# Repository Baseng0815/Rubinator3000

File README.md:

##### GYMNASIUM EDERTALSCHULE, FRANKENBERG-HESSEN

# Jugend forscht 2020

```
Philipp Geil, 19 Jahre
Tim Depner, 18 Jahre
Bastian Engel, 19 Jahre
```
## Das Lösen eines Zauberwürfels

## - der Rubinator3000 -

Mathematik-Informatik
Projektbetreuer: Oliver Blinn, Edertalschule Frankenberg

## Kurzfassung

Bei unserem Projekt “​ _Das Lösen eines Zauberwürfels - der Rubinator3000_ ​”
versuchten wir, einen verdrehten Zauberwürfel automatisch zu lösen.
Dazu haben wir Software und Hardware entwickelt, die einen Würfel erkennen,
verarbeiten und einen Lösealgorithmus anwenden können.
Anforderungen an die Hardware:
● Drehung jeder Seite des Würfels mit Schrittmotoren
● Elektronik zur Steuerung der Motoren
● Kameras zur Erkennung des verdrehten Würfels
Anforderungen an die Software:
● Auswertung der Kamerabilder und programmiertechnische Darstellung des
Würfels
● Lösealgorithmus entwickeln und Lösezüge berechnen
● Lösezüge am Würfel ausführen
...und natürlich das Vereinen aller Hardware-Komponenten in einer Maschine sowie
dessen Kommunikation mit dem Rechner, auf welchem die Steuerungssoftware
mit grafischer Benutzeroberfläche läuft.

## Erfolge:
1. Preis Regionalwettbewerb 2020
SMA Innovationspreis
Qualifikation Landeswettbewerb, der allerdings aufgrund von Corona abgesagt wurde

## 1. Einleitung

#### 1.1 Wieso einen Zauberwürfel lösen?

Unsere Faszination für Zauberwürfel hat vor ungefähr einem Jahr angefangen, als
wir bei einer extrakurrikularen E-Technik-Vorlesung ein YouTube-Video (Q1) sahen,
in dem jemand einen Zauberwürfel in 4.73 Sekunden löst. Da haben wir uns gefragt,
wie so etwas überhaupt möglich ist. Wir haben es als Kinder selbst probiert und
sogar bis zu drei Seiten gelöst bekommen, aber vollständig klappte es nie. Bei
nachfolgender Recherche im Internet sind wir auf Methoden gestoßen, welche von
sogenannten “Speedcubern” verwendet werden, um den Würfel in einer unglaublich
kurzen Zeit zu lösen.
Vertieft wurde unser Interesse weiter durch die unzähligen Variationen des Würfels.
Abseits der bekannten 3x3-Version ist der Zauberwürfel auch in einigen anderen
Größen von 2x2 bis zu 15x15 erhältlich. Dazu gibt es das Drehpuzzle nicht nur in
Hexaeder-Form, sondern auch in anderen polyedrischen Formen, wie beispielsweise
dem Tetraeder. Einige stellen sich sogar der Herausforderung, den Würfel mit nur
einer Hand, mit den Füßen oder mit verbundenen Augen zu lösen.
Wir selbst schaffen es per Hand, den Zauberwürfel in einer Zeit von circa 45
Sekunden zu lösen. Schaffen wir es, diese Zeit mit unserer Maschine zu
unterbieten?

#### 1.2 Gängige Lösemethoden

Die Lösung des Zauberwürfels erfolgt nicht improvisiert, sondern läuft nach einem
strikten Schema. Dies ist notwendig, um bereits gelöste Teile nicht erneut zu
verdrehen. Manche Teile lassen sich zwar ohne Vorkenntnisse lösen, aber den
Hauptteil löst man mit vorher entwickelten und auswendig gelernten Algorithmen und
Methoden, die den Würfel auf eine bestimmte Art und Weise permutieren.
Die am häufigsten verwendeten Lösemethoden sind zum einen die
“Fridrich”-Methode, welche von Jessica Fridrich entwickelt wurde, und zum anderen
die “Layer-by-Layer”-Methode.
Die Fridrich-Methode enthält viele Algorithmen, die man auswendig lernen muss,
welche jedoch eine kurze Lösezeit garantieren, weshalb sie auch von Speedcubern
verwendet wird.
Die Layer-by-Layer-Methode ist einfacher zu erlernen, erfordert aber mehr Züge, was
die Lösezeit natürlich verlängert.

- Kurzfassung
- 1. Einleitung
      - 1.1 Wieso einen Zauberwürfel lösen?
      - 1.2 Gängige Lösemethoden
      - 1.3 Das Ziel der Arbeit
- 2. Vorgehensweise, Materialien und Methode
      - 2.1 Die Position der Farben auf dem Würfel
      - 2.2 Drehungen der Seiten
      - 2.3 Die Lösung des Zauberwürfels
      - 2.3.1 Das weiße Kreuz
      - 2.3.2 Das F2L
      - 2.3.4 Die letzte Seite
      - 2.4 Die Entwicklung der Software
      - 2.5 Die Entwicklung der Hardware
      - 2.6 Der Bau der Hardware
      - 2.7 Die Digitalisierung des Würfels
- 3. Ergebnisse
      - 3.1 Software
      - 3.2 Hardware
- 4. Ergebnisdiskussion
- 5. Zusammenfassung
- 6. Danksagung
- 7. Quellen- und Literaturverzeichnis

Layer-by-Layer-Methode (Q3)
Ausgang Weißes
Kreuz
Weiße
Ecksteine
Mittlere
Schicht
Gelbes
Kreuz
Gelbe
Ecksteine
Ecksteine
drehen
Fridrich-Methode (Q4)
Ausgang Weißes Kreuz “First two
layers” (F2L)
“Orient last
layer” (OLL)
“Permutate
last layer”
(PLL)
Man erkennt, dass die Fridrich-Methode weniger Schritte benötigt. Dadurch wird sie
jedoch auch komplizierter und schwieriger zu erlernen. Die Layer-by-Layer-Methode
erfordert neun verschiedene Algorithmen, während es bei der Fridrich-Methode
schon 78 sind.

#### 1.3 Das Ziel der Arbeit

Wie schon erwähnt, brauchen wir ganze 45 Sekunden, um den Zauberwürfel per
Hand zu lösen und vergessen häufig Algorithmen. Diesen Problemen wollen wir
durch maschinelles Lösen entgegentreten. Motoren können die Drehungen am
Würfel besser koordinieren als wir mit unseren Händen. Außerdem können Rechner
Algorithmen ohne Probleme speichern und ausführen. Besonders beeindruckt hat
uns dabei der Löseroboter von Ben Katz, welcher in der Lage ist, den Würfel in 0.
Sekunden zu lösen (Q5).
Unser Ziel ist es, den Zauberwürfel innerhalb von 30 Sekunden lösen zu können, d.h.
konkret, eine dafür nötige Farberkennung zu entwickeln, eine entsprechende
Lösesoftware zu schreiben und eine Ansteuerung zu bauen, welche diese
Anforderung erfüllen kann.

## 2. Vorgehensweise, Materialien und Methode

#### 2.1 Die Position der Farben auf dem Würfel

Sei die Menge der Seiten des Würfels und die Menge der Flächen einer Seite.
Damit sind die Positionen der einzelnen Flächen auf dem Würfel bestimmt durch:
Um den Würfel darstellen zu können, müssen die Positionen noch durch die Menge
der Farben des Würfels ergänzt werden:
Damit besteht die Darstellung des Würfels aus einem Array der Länge 6, in welchem
die neun Farbwerte für jede Seite gespeichert sind. Das Programm geht davon aus,
dass sich die orange Fläche links befindet und die weiße Fläche oben. Da die
Implementation des Lösungsalgorithmus leichter fällt, wenn man nicht mit den
einzelnen Flächen arbeitet, sondern jene Flächen zu Steinen zusammenfasst,
welche über die Würfelkanten aneinander grenzen, haben wir uns dazu entschieden,
eine Struktur für die Ecksteine (3 Flächen) und eine für die Kantensteine (2 Flächen)
zu erstellen. In diesen Strukturen werden ein Tupel der Farben des Steines sowie ein
Verweis auf den Würfel, zu dem dieser Stein gehört, gespeichert. Die Steine werden
bei der Initialisierung der Cube-Klasse automatisch aus den vorgegebenen
Positionen erstellt, die für jeden Stein festgelegt sind. Die Steine werden durch ihre
Farben charakterisiert, da die Positionen zum einen durch die Indizes des Arrays
festgelegt sind und es zum anderen für den Lösungsalgorithmus nötig ist, die
Position gewisser Steine anhand der Farben zu identifizieren. Diese Positionen
lassen sich durch einen Vergleich der Farben des Steines mit den vorgegebenen
Steinpositionen bestimmen.

#### 2.2 Drehungen der Seiten

Um den Zauberwürfel nun zu lösen oder zu verdrehen, mussten wir also noch eine
Möglichkeit implementieren, um einzelne Seiten des Würfels im Programm zu
drehen. Eine Drehung wird durch die zu drehende Seite und die Anzahl der
Vierteldrehungen (90°) im Uhrzeigersinn festgelegt.
Jeder Move beschreibt eine bestimmte Permutation des Würfels, da zum einen die
Farben auf der jeweiligen Seite, aber auch teilweise die Farben auf den
angrenzenden Seiten vertauscht werden.

Diese beiden Permutationen können jeweils durch Funktionen beschrieben werden:
Betrachtet man die Drehung einer Seite im Uhrzeigersinn, so lässt sich
bestimmen:
Der Funktionswert von _f_ 1 gibt hierbei die neue Position nach der Drehung an:
Die Funktionswerte von lassen sich nicht allgemein formulieren, da abhängig
von der gedrehten Seite ist. Die Relationen von sind im Programm hinterlegt und
werden auf die entsprechenden Seiten angewendet.

#### 2.3 Die Lösung des Zauberwürfels

#### 2.3.1 Das weiße Kreuz

Das weiße Kreuz wird durch ein Objekt der “CrossSolver”-Klasse gelöst. Dazu wird
zuerst ein Pivotelement festgelegt. Bei diesem Element handelt es sich entweder um
einen weißen Kantenstein, der sich bereits richtig auf der weißen Seite befindet und
bei dem sich die meisten Steine in der gewünschten Position befinden, oder um
einen weißen Kantenstein, der sich mit den wenigsten Zügen in die richtige Position
bringen lässt. Um die Anzahl der Züge zu bestimmen, die benötigt werden, um den
Stein relativ zum Pivotelement richtig auszurichten, gibt es eine Methode, die jeden
Stein bewertet und die Anzahl der Züge zurückgibt. Beim Lösen des weißen Kreuzes
bewertet der “CrossSolver” zuerst für jeden Kantenstein, wie viele Züge jeweils
benötigt werden und löst dann den Kantenstein, für den die wenigsten benötigt
werden. Zum Lösen der einzelnen Steine unterscheidet der “CrossSolver” zwischen
vier verschiedenen Fällen:

1. Der Stein befindet sich mit der weißen Fläche auf der weißen Seite, aberdie
    seitliche Farbe stimmt nicht.
2. Der Stein befindet sich mit der weißen Fläche auf der unteren Seite.
3. Der Stein befindet sich auf der mittleren Ebene, also mit keiner Fläche auf
    der oberen oder unteren Seite.
4. Der Stein befindet sich mit der weißen Fläche auf einer der seitlichen Seiten
    (orange, grün, rot, blau) und mit der anderen Fläche auf der oberen oder
    unteren Seite.
Die einzelnen Fälle werden dann durch vorgegebene Algorithmen gelöst.

#### 2.3.2 Das F2L

Das Lösen des F2L funktioniert analog zum Lösen des weißen Kreuzes. Das
Programm orientiert sich hier nun nicht mehr an nur einem Stein, sondern an jeweils
zwei Steinen, die gelöst werden sollen. Dazu bewertet es wieder jedes Steinpaar und
löst jenes, welches die wenigsten Züge benötigt. Diese Berechnung erfolgt
asynchron, um Rechenzeit zu sparen. Danach wird das Paar mit Hilfe von 13
Algorithmen gelöst.

#### 2.3.4 Die letzte Seite

Für das Lösen der letzten Seite sind im Programm Muster und die dazugehörigen
Zugfolgen hinterlegt (57 OLL und 21 PLL). Die Muster für das OLL beziehen sich nur
auf die Anordnung der gelben Flächen. Dazu wird eine Folge von 9 Bits verwendet,
welche die gelbe Seite repräsentiert, und jeweils vier Folgen von je 3 Bits, welche die
3 Flächen der über die Würfelkanten angrenzenden Seiten repräsentieren. Das
Programm vergleicht dann jegliche Muster mit dem Würfel und kann somit die
Zugfolge angeben. Die PLL-Muster sind etwas komplexer als die OLL-Muster, da das
PLL die einzelnen Farben einbezieht. Dazu wird jeder der vier seitlichen Farben eine
Zahl zugeordnet ((orange, 0), (grün, 1), (rot, 2), (blau, 3)). Im Programm sind dann
die Differenzen zwischen den drei Steinen für alle vier Seiten hinterlegt. Mit diesen
Mustern kann daraufhin die Zugfolge bestimmt werden, die zur Lösung des
Zauberwürfels führt.

#### 2.4 Die Entwicklung der Software

Wir haben mithilfe von Visual Studio Community 2019, einer von Microsoft
entwickelten IDE, programmiert. Das Projektmanagement wird dadurch vereinfacht
und der integrierte Designer erlaubt einfache und gute GUI-Erstellung. Da jeder von
uns schon im Voraus Erfahrung mit dieser Entwicklungsumgebung hatte, mussten
wir uns nicht umstellen und der Entwicklungsprozess konnte sofort starten.
Als Programmiersprache entschieden wir uns für C#, um WPF (Windows
Presentation Foundation) nutzen zu können. Das ist eine GUI-Library, mit der viele
Windows-Programme geschrieben werden. Ein großer Vorteil davon ist, dass das
GUI-Design extern in XAML-Dateien definiert und damit vollständig von der Logik
des Programms abgekoppelt ist. Dies ermöglichte uns, die Arbeit besser aufzuteilen.
So kann ein Programmierer am GUI arbeiten, während ein anderer die Logik dazu
schreibt. Die 2D-und 3D-Ansicht des Würfels erstellten wir mit OpenGL, einer
Graphics-Library, die auch in vielen Computerspielen verwendet wird und sehr
weitreichende Funktionen besitzt.

Da wir zu dritt waren und viele Änderungen parallel zusammenkamen, benötigten wir
ein Versionskontrollsystem, um diese zu verwalten und gegebenenfalls bei Bugs
frühere Versionen wiederherstellen zu können. Entschieden haben wir uns für Git,
welches auch industriell verwendet wird. Damit war es kein Problem mehr, Aufgaben
aufzuteilen und zu synchronisieren.

#### 2.5 Die Entwicklung der Hardware

Das CAD-Modell unseres ​ _“Rubinator3000”_ haben wir mit dem kostenlosen Programm
“FreeCAD” entworfen, da dieses für unsere Anforderungen genügt und wir unser
Projekt kostengünstig gestalten wollten. Zudem war es uns mit FreeCAD möglich, die
Bauteile in das STL-Format zu exportieren, um sie mit einem 3D-Drucker drucken zu
können. Da unsere Hardware fast ausschließlich aus 3D-Druck Bauteilen besteht,
war diese Funktion sehr hilfreich. Die Schaltpläne für die Ansteuerung der
Schrittmotoren erstellten wir mit Eagle. Eagle bietet zudem die Möglichkeit,
Leiterplatten zu designen, um diese bei einem Leiterplattenhersteller anfertigen zu
lassen.
Die Ansteuerung der Schrittmotoren musste über eine Verstärkerschaltung getätigt
werden. Das lag zum einen daran, dass die Schrittmotoren eine Spannung von 12V
benötigen, während der Arduino nur 5V liefert. Zum anderen wird ein sehr großer
Strom benötigt, um die Magnetfelder innerhalb der Schrittmotoren mit Hilfe von
Spulen zu erzeugen.

#### 2.6 Der Bau der Hardware

Wir haben uns für 3D-gedruckte Bauteile
entschieden, da diese eine höhere Präzision
der Mechanik ermöglichten. Unser erster
Prototyp bestand ausschließlich aus Holz
und es kam aufgrund mangelhafter
Genauigkeit der Mechanik zum
sogenannten “Verkantungsproblem”: Eine
Seite des Würfels verkantete sich nach einer
unvollständigen Drehung. Dieses Problem
lösten wir letztendlich durch die zweite
Version der Hardware und einen anderen Zauberwürfel. Zudem ließen die
verwendeten Miniaturbalg-Kupplungen zu viel Spielraum zu, was zu
Ungenauigkeiten bei den Würfeldrehungen führte. Deshalb ersetzten wir sie durch
Elastomerkupplungen, da diese deutlich genauer sind, wodurch sich der Würfel viel
besser drehen lässt.
Zudem haben wir uns Platinen zur Ansteuerung der Schrittmotoren anfertigen
lassen, da die anfangs selbst gelöteten Platinen teilweise unzuverlässig waren und
sehr viel Platz im Gehäuse in Anspruch nahmen. Hinzu kam noch, dass die selbst
gelöteten Platinen viel Wärme entwickelten, da jede einzelne von ihnen einen

separaten Spannungsregler besaß, der für den Anschluss eines Mikrocontrollers
gedacht war.
Im nebenstehenden Bild ist eine
Schaltung abgebildet, welche zeigt,
wie mithilfe des Transistors (T1) der
Stromkreis der Spule des
Schrittmotors (L1) geschlossen wird^1.
Dadurch wird es möglich, dass Strom
fließen kann, welcher das
magnetische Feld im Schrittmotor
erzeugt. Der Basiswiderstand (R1)
dient zur Begrenzung des
Basisstroms des Transistors, da der
Ausgang des Arduino einen Strom
von maximal 40mA zur Verfügung
stellt.
Wir ließen die Bodenplatte bei der Firma Viessmann drucken, weil diese für unseren
3D-Drucker zu groß war. Sie stellte uns für diesen Druck einen besseren 3D-Drucker
zur Verfügung. Nach dem Druck haben wir sie auf eine solide Holzbox gesetzt,
welche auch die Elektronik enthält. Dadurch wird Stabilität garantiert und die Motoren
können passend positioniert werden.

#### 2.7 Die Digitalisierung des Würfels

Unsere erste Methode zur Digitalisierung des Würfels sah folgendermaßen aus:

(^1) Die Freilaufdiode wurde zur Vereinfachung der Schaltung weggelassen

Wir lasen jede einzelne Seite mit der Kamera eines Smartphones ein, um daraus den
Würfel digital zusammensetzen zu können. Dafür haben wir eine Android-App in der
Programmiersprache Java geschrieben.
Ein Computer – also auch das Smartphone, welches wir benutzen – stellt Farben im
RGB-Format dar. Anhand dieser Werte werden die einzelnen Würfel-Farben
(Orange, Weiß, Grün, Gelb, Rot und Blau) auch unterschieden.
Um sich auch wechselnden Lichtverhältnissen anpassen zu können, war es nötig zu
Beginn Referenz-RGB-Werte festzulegen, anhand welcher die App die Farben
unterschied.
Im nächsten Schritt hielten wir die Handykamera vor jede Würfelseite. Die App las
die RGB-Werte der einzelnen Flächen aus und ordnete ihnen anhand der anfangs
eingelesenen Referenz-RGB-Werten die entsprechende Farbe zu.
Sobald die App eine Würfelseite eingelesen hatte, schickten wir dessen Farben über
ein WLAN-Netzwerk an jenen Laptop, auf welchem das Hauptprogramm lief.
Nachdem wir auf diese Weise alle sechs Seiten eingelesen und an den Laptop
geschickt hatten, könnte dieser daraus den Würfel digital zusammensetzen.
Die zweite Version unseres Projekts brachte auch ein Upgrade in der Farberkennung
mit sich. Anstatt mit einer Handy-App jede Seite einzeln einzulesen, brachten wir vier
stationäre USB-Kameras an der Maschine an, mit welchen wir die RGB-Werte der
einzelnen Flächen des Würfels automatisch einlesen. Dies beschleunigt den Prozess
der Digitalisierung des Würfels natürlich enorm.
Auch an der Erfassung und Verarbeitung der eingelesenen RGB-Werte haben wir
Änderungen vorgenommen:
Für jede einzelne Fläche des Würfels
legen wir eine Position auf einem der 4
Kamera-Streams fest, an welcher die
RGB-Werte der jeweiligen Fläche
ausgelesen werden sollen. Da die 8
Mittelsteine des Würfels ihre Position
während des Drehen nie verändern,
werden deren RGB-Werte gar nicht mehr
eingelesen.
So lesen wir alle RGB-Werte an den 48
Positionen ein und berechnen die
jeweilige Wahrscheinlichkeit dafür, dass
die jeweiligen RGB-Werte zu einer orangen, weißen, grünen, gelben, roten oder
blauen Fläche gehören.
Die 8 Flächen an den Positionen mit den höchsten Orange-Wahrscheinlichkeiten
bestimmen wir als orange Flächen. So gehen wir die restlichen 5 Farben ebenfalls
durch und haben zum Schluss 8 Flächen von jeder Farbe, mit welchen wir wiederum
den Würfel digital darstellen.

Durch dieses Verfahren wird die Farberkennung viel präziser, da wir davon
ausgehen, dass wir genau 8 Flächen von allen Farben haben.
Ein Problem, welches wir bei der Farberkennung hatten war Folgendes:
Aufgrund der sehr glatten Oberfläche der Würfelflächen, spiegelten diese das
Umgebungslicht teilweise gebündelt direkt in eine der Kameralinsen. Dadurch war im
Kamerabild nicht die entsprechende Farbe der Seite zu sehen, sondern ein helles,
weißliches Leuchten. Dies verfälschte die RGB-Werte, welche für die dazugehörige
Fläche eingelesen wurden. Eine eigentlich blaue Fläche erschien somit
unerwünschterweise weiß. Wir haben dieses Problem gelöst, indem wir einen
Vorhang über die ganze Maschine gehängt haben, um den Spiegelungseffekt zu
minimieren. Damit wir jedoch überhaupt noch etwas mit den Kameras sehen können,
haben wir zusätzlich LEDs direkt in die Maschine gebaut, welche den Würfel mit
diffusem Licht bescheinen.
Dies soll jedoch nur vorübergehend die Lösung des Problems sein, da das Abdecken
und das Entfernen der Abdeckung recht viel Zeit braucht. Für die Zukunft planen wir,
nicht absolute Positionen, an welchen die Farben des Würfels ausgelesen werden,
zu benutzen. Stattdessen soll das Programm mittels Konturerkennung selbst
herausfinden, wo sich auf dem entsprechenden Kamerabild die einzelnen
Würfel-Flächen befinden, von welchen das Programm daraufhin die entsprechenden
Farben ausliest. Hierbei könnten wir zu helle Pixel aussortieren, wodurch das
“Spiegelungs-Problem” gelöst würde. Erste Tests in separat von uns programmierten
Anwendungen liefern vielversprechende Ergebnisse. Jetzt gilt es noch, die neue
Farberkennung in das Hauptprogramm zu implementieren.

## 3. Ergebnisse

#### 3.1 Software

Wir haben mithilfe der vorgestellten Vorüberlegungen und Methoden das
Hauptprogramm fertiggestellt, welches den Würfel lösen und die Lösealgorithmen
über eine serielle Schnittstelle an den Arduino schicken kann.
Die Effizienz der Algorithmen lässt sich an folgendem Graph ablesen:
Für jede Verdrehungsanzahl machten wir 30
Testdurchgänge, woraufhin daraus der
Mittelwert gebildet wurde. Die
Schwankungen lassen sich dadurch erklären,
dass nur ein einziger zusätzlich ausgeführter
Algorithmus mehrere Züge enthält und
dadurch das Ergebnis stark beeinflusst
werden kann.
Es ist zu erkennen, dass unsere Lösung ab
vier Verdrehungen erheblich mehr Züge
benötigt. Ab sechs Verdrehungen pendelt sich
die Anzahl der Lösezüge auf ungefähr 65 ein.
Die Schrittmotoren lassen sich mit 360° pro Sekunde drehen, was zwei Zügen
entspricht. Daher ist eine theoretische Lösezeit von ca. 15 Sekunden erreichbar, die
aber durch Ausnahmefälle wie zum
Beispiel die Doppeldrehung einer
Seite oder dem ​ _Multiturning_
Schwankungen unterliegt.
Außerdem ist zu erkennen, dass
der Zugzuwachs am stärksten vom
FTL beeinflusst wird, wobei die
OLL- und PLL-Algorithmen gegen
Ende weniger beitragen. Das Kreuz
hat kaum Einfluss.
Die grafische Oberfläche des
Programms enthält alle nötigen
Kontrollelemente, so zum Beispiel
das Verdrehen oder Lösen des Würfels oder Debug-Fenster zum Beheben von
fehlerhaften Algorithmen und Mustern. Dadurch können wir leicht und ohne

ständiges Überlegen Einstellungen ändern und Tests durchführen. Das ist zum
Beispiel besonders relevant für die Verbindung zum Mikrocontroller, da diese über
einen sich ändernden COM-Port stattfindet, welchen man anfangs auswählen muss.

#### 3.2 Hardware

Der Arduino wartet nach dem Verbinden mit dem Programm auf die Befehle und
führt diese aus. Er ist nötig, da die Schrittmotoren nicht direkt an den Computer
angeschlossen
werden können.
Zudem benötigen die
Schrittmotoren sehr
viel Strom. Deshalb ist
es notwendig, für
jeden Schrittmotor
eine Schaltung zu
bauen, die genug
Strom liefern kann,
um den Würfel zu
drehen. Anfangs
hatten wir die Motoren
nach einer Drehung
nicht abgeschaltet und
so entstand das
Problem, dass alle
inaktiven Motoren zu

viel Strom verbrauchten und somit nicht genug Drehmoment bereitstand, um den
Würfel zu drehen. Dieses Problem haben wir softwaretechnisch gelöst, indem wir
den Strom der Motoren nach jeder Drehung abschalteten und so der komplette
Strom des Netzgerätes für einen oder bei Multiturns zwei Motoren bereitsteht.

## 4. Ergebnisdiskussion

Unser ​ _“Rubinator3000”_ ist noch nicht das perfekte Ergebnis jahrelanger Forschung,
aber es kann sich trotzdem sehen lassen.
Wie anfangs bereits erwähnt, kam uns die Idee zum Bau einer solchen Maschine, bei
einer extrakurrikularen E-Technik-Vorlesung im Rahmen der Young Engineer
Academy (YEA). Wir haben dort überlegt, was wir als unser Abschlussprojekt bei der
YEA realisieren könnten. Da wir noch viel Zeit hatten, bis das Projekt vorgestellt
werden sollte, entschieden wir uns nach einigen Suchanfragen im Internet für den
Bau eines doch recht aufwendigen Zauberwürfel-Lösers. Einige weitere
Kursteilnehmer, welche sich ebenfalls für den Zauberwürfel begeistern, unterstützten
unsere Idee.
Anfangs schien unsere Aufgabe recht simpel, da man lediglich 6 Schrittmotoren
benötigte, die die Seiten des Zauberwürfels drehen sollten.
Bereits in den nächsten Wochen (Januar 2019) starteten wir mit der
Programmierung. Der eigentliche Bau der ersten Maschine begann dann Ende April
2019 und pünktlich zum Präsentationstermin am 28. Juni vollendeten wir die erste
Version der Hardware. Bis dahin hatten wir während der Schulzeit schon dutzende
Freistunden in unser Projekt investiert, da die Umsetzung des Projekts dann doch
komplizierter war, als wir zunächst vermutet hatten. Vor allem die Drehung des
Würfels machte uns zu schaffen, da die Hardware zu ungenau war und der Würfel
sich deshalb immer wieder verkantete. Dies war aber letztendlich nicht das größte
Problem, welches wir bei der Präsentation hatten.
Auf der Bühne scheiterte die Vorführung unserer Maschine am Lösen des
Zauberwürfels durch das Programm.
Also entschlossen wir uns, in den Sommerferien das Programm zu überarbeiten. Da
der bestehende Code mittlerweile sehr unübersichtlich war und wir nicht genau
wussten, wo die einzelnen Fehler lagen, entschlossen wir uns dazu, das Programm
von Grund auf neu zu entwickeln. Wir besaßen bereits das Vorwissen aus dem
ersten Versuch , weshalb uns die Entwicklung der zweiten Maschine leichter fiel.
Aufgrund der Verkantungen des Würfels kam uns die Idee, die Teile der Hardware,
welche eine hohe Genauigkeit erforderten, mit dem 3D-Drucker zu fertigen, da dieser
viel genauere Ergebnisse liefert als das Aussägen aus Holz. Zudem haben wir neue
Kupplungen eingebaut, die zur Erhöhung der Genauigkeit beitrugen.

Das Projekt erschien uns auf den ersten Blick leicht, aber es gab viele Faktoren, die
wir nicht berücksichtigt hatten. Darunter fiel zum Beispiel das Einlesen des Würfels,
das Bauen der Hardware mit einer hohen Genauigkeit und vieles andere.
Die Software könnte noch verbessert werden, indem man beispielsweise eine andere
Methode zum Lösen des Würfels verwendet, die weniger Züge benötigt. Diese
Verbesserung würde das maschinelle Lösen auch erheblich beschleunigen, da sich
die Motoren dadurch weniger drehen müssten.
Zudem könnte man auch Motoren verwenden, die sich schneller ansteuern lassen,
welche ebenfalls das Lösen beschleunigen würden.
Wir hatten während der Entwicklung die Idee das Hauptprogramm auf einem
Raspberry Pi laufen zu lassen, da dieser den Computer ersetzen würde, der die
Lösung berechnet. Diese Idee verwarfen wir aber schnell, da wir schon angefangen
hatten, die Software auf dem .NET Framework von Microsoft für Windows zu
entwickeln, während der Raspberry auf einem linuxbasierten Betriebssystem läuft.
Der Ansatz könnte aber in der Zukunft realisiert werden.
Auch die Ansteuerung der Motoren hat uns Probleme bereitet, da wir eine eigene
Platine entwickelt und einen Mikrocontroller programmiert haben. Dieser ist jedoch
beim Debuggen der Software durch eine Überspannung kaputt gegangen und wir
mussten ihn durch einen Arduino ersetzen.

## 5. Zusammenfassung

Zusammenfassend lässt sich sagen, dass unser Projekt noch viele
Erweiterungsmöglichkeiten bietet. Es könnten beispielsweise noch LEDs eingebaut
werden, die für eine bessere Beleuchtung des Würfels bei schlechten
Lichtverhältnissen sorgen.
Unser Ziel, dass unsere Maschine weniger Zeit zum Lösen des Würfels benötigt als
wir selbst per Hand, hat das Projekt noch nicht ganz erreicht. Es befindet sich aber
auf einem guten Weg zu einer Lösung, die unseren ursprünglichen Anforderungen
gerecht wird. Dies könnte durch weitere Verbesserungen der Hard- und Software
erreicht werden.
Das Projekt ​ _“Rubinator3000”_ hat zwar nur einen kleinen Nutzen für die Allgemeinheit,
aber es hat uns geholfen, unsere Kompetenzen im Bereich der Programmierung und
der Entwicklung von Hardware zu erweitern. Zudem haben wir die Erfahrung
gemacht, dass Dinge und Ideen oft einfacher erscheinen, als sie es eigentlich sind.
Es lohnt sich also, zuerst darüber nachzudenken, wie man sie angeht und realisiert.
Zuletzt durften wir die Erfahrung machen, was man mit Teamwork alles erreichen
kann. Während des Entwicklungsprozesses haben sich alle Team-Mitglieder nur auf

jeweils ein Teilgebiet spezialisiert. Trotzdem können wir durch unsere gelungene
Zusammenarbeit nun einen voll funktionsfähigen Zauberwürfellöser präsentieren.

## 6. Danksagung

Abschließend bedanken wir uns für jegliche Unterstützung während der Umsetzung
unseres Projekts.
Exemplarisch möchten wir hier die Fachschaft Physik der Edertalschule nennen,
welche uns bei Fragen in der Umsetzung beriet und uns kostenlos über einen
längeren Zeitraum den Zugang zu ihrem Werkraum gewährte, in welchem wir unsere
Maschine entwickeln und anfertigen konnten. Zudem danken wir unseren
Mitschülern der Young Engineer Academy, die uns beim Bau der ersten Version des
“Rubinator3000” unterstützt haben.
Darüber hinaus geht ein riesiges Dankeschön an die Viessmann Group, welche uns
finanziell bei der Anfertigung der Hardware unterstützte. Zusätzlich ermöglichte sie
uns die Teilnahme an der Young Engineer Academy, durch welche wir essentielle
Grundkenntnisse und letztendlich auch die Idee für dieses Projekt bekommen haben.

## 7. Quellen- und Literaturverzeichnis

##### Q1: 04.01.2020 16: https://www.youtube.com/watch?v=KfpJZHP6DLA
##### Q2: 04.01.2020 17: https://speedcube.de/
##### Q3: 04.01.2020 17: https://ruwix.com/the-rubiks-cube/how-to-solve-the-rubiks-cube-beginners-method/
##### Q4: 04.01.2020 17: https://ruwix.com/the-rubiks-cube/advanced-cfop-fridrich/
##### Q5: 04.01.2020 17: https://www.youtube.com/watch?v=nt00QzKuNVY
##### Q6: 14.01.2020 19: https://www.arduino.cc/en/Tutorial/DigitalPins

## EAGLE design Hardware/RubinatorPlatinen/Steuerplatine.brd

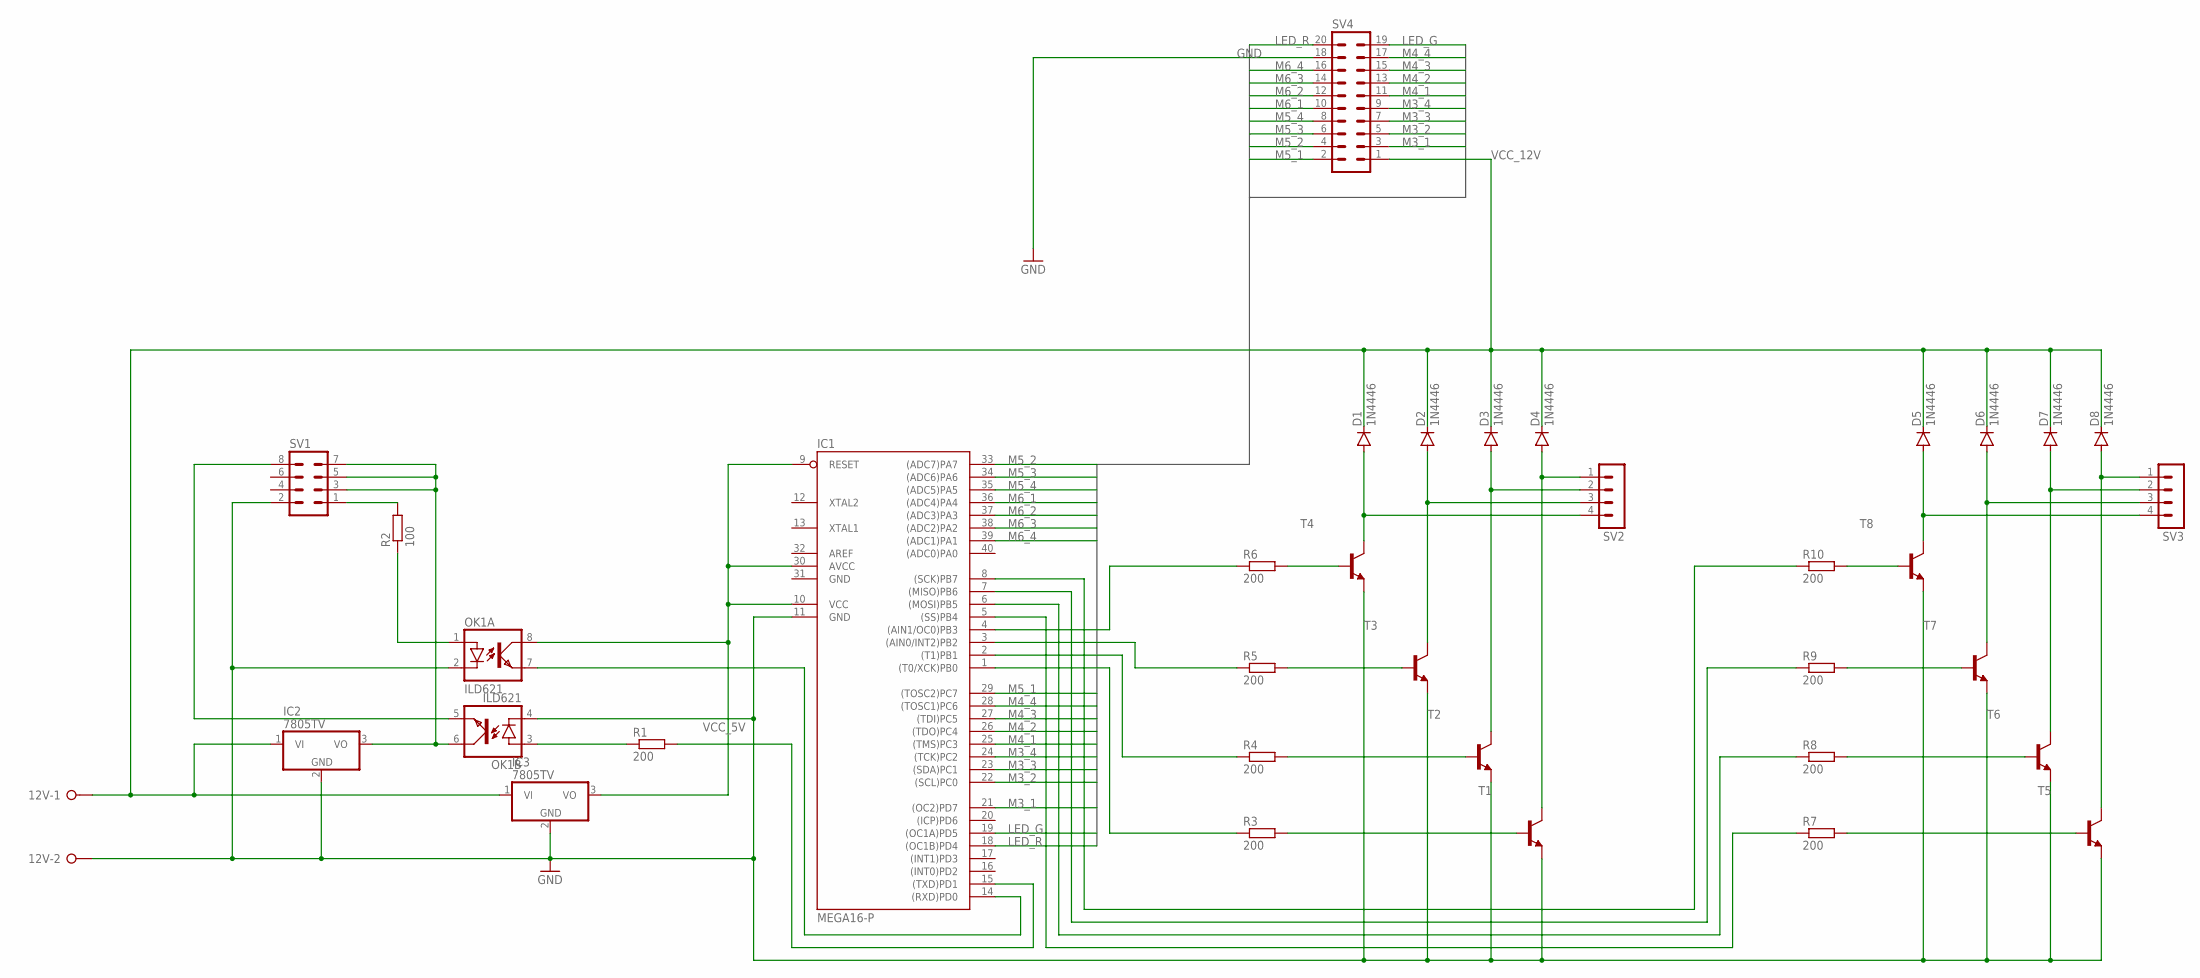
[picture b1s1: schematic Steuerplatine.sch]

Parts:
12V: W237-02P; W237-132
D1, D2, D3, D4, D5, D6, D7, D8: 1N4446; DO35-10
IC1: MEGA16-P; DIL40
IC2, IC3: 7805TV; TO220V
OK1: ILD621; DIL08
R1, R3, R4, R5, R6, R7, R8, R9, R10: 200; 0207/10
R2: 100; 0207/10
SV1: MA04-2
SV2, SV3: MA04-1
SV4: MA10-2
T1, T2, T3, T4, T5, T6, T7, T8: -NPN-TO126V; TO126V

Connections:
GND: 12V.2, IC1.11 (GND), IC1.31 (GND), IC2.2 (GND), IC3.2 (GND), OK1.2 (C), OK1.4 (C), SV1.2, SV4.18, T1.1 (E), T2.1 (E), T3.1 (E), T4.1 (E), T5.1 (E), T6.1 (E), T7.1 (E), T8.1 (E)
LED_G: IC1.19 ((OC1A)PD5), SV4.19
LED_R: IC1.18 ((OC1B)PD4), SV4.20
M3_1: IC1.21 ((OC2)PD7), SV4.3
M3_2: IC1.22 ((SCL)PC0), SV4.5
M3_3: IC1.23 ((SDA)PC1), SV4.7
M3_4: IC1.24 ((TCK)PC2), SV4.9
M4_1: IC1.25 ((TMS)PC3), SV4.11
M4_2: IC1.26 ((TDO)PC4), SV4.13
M4_3: IC1.27 ((TDI)PC5), SV4.15
M4_4: IC1.28 ((TOSC1)PC6), SV4.17
M5_1: IC1.29 ((TOSC2)PC7), SV4.2
M5_2: IC1.33 ((ADC7)PA7), SV4.4
M5_3: IC1.34 ((ADC6)PA6), SV4.6
M5_4: IC1.35 ((ADC5)PA5), SV4.8
M6_1: IC1.36 ((ADC4)PA4), SV4.10
M6_2: IC1.37 ((ADC3)PA3), SV4.12
M6_3: IC1.38 ((ADC2)PA2), SV4.14
M6_4: IC1.39 ((ADC1)PA1), SV4.16
unnamed: R10.2, T8.3 (B)
unnamed: IC2.3 (VO), OK1.6 (COL), SV1.3, SV1.5, SV1.7
unnamed: R2.2, SV1.1
unnamed: IC1.14 ((RXD)PD0), OK1.7 (EMIT)
unnamed: IC1.15 ((TXD)PD1), R1.2
unnamed: OK1.3 (A), R1.1
unnamed: OK1.5 (EMIT), SV1.8
unnamed: OK1.1 (A), R2.1
unnamed: R6.2, T4.3 (B)
unnamed: R5.2, T3.3 (B)
unnamed: R4.2, T2.3 (B)
unnamed: R3.2, T1.3 (B)
unnamed: IC1.1 ((T0/XCK)PB0), R3.1
unnamed: IC1.2 ((T1)PB1), R4.1
unnamed: IC1.3 ((AIN0/INT2)PB2), R5.1
unnamed: IC1.4 ((AIN1/OC0)PB3), R6.1
unnamed: D3.A, SV2.2, T2.2 (C)
unnamed: D4.A, SV2.1, T1.2 (C)
unnamed: D2.A, SV2.3, T3.2 (C)
unnamed: D1.A, SV2.4, T4.2 (C)
unnamed: R9.2, T7.3 (B)
unnamed: R8.2, T6.3 (B)
unnamed: R7.2, T5.3 (B)
unnamed: D6.A, SV3.3, T7.2 (C)
unnamed: IC1.5 ((SS)PB4), R7.1
unnamed: IC1.6 ((MOSI)PB5), R8.1
unnamed: IC1.7 ((MISO)PB6), R9.1
unnamed: IC1.8 ((SCK)PB7), R10.1
unnamed: D7.A, SV3.2, T6.2 (C)
unnamed: D8.A, SV3.1, T5.2 (C)
unnamed: D5.A, SV3.4, T8.2 (C)
VCC_5V: IC1.9 (RESET), IC1.10 (VCC), IC1.30 (AVCC), IC3.3 (VO), OK1.8 (COL)
VCC_12V: 12V.1, D1.C, D2.C, D3.C, D4.C, D5.C, D6.C, D7.C, D8.C, IC2.1 (VI), IC3.1 (VI), SV4.1

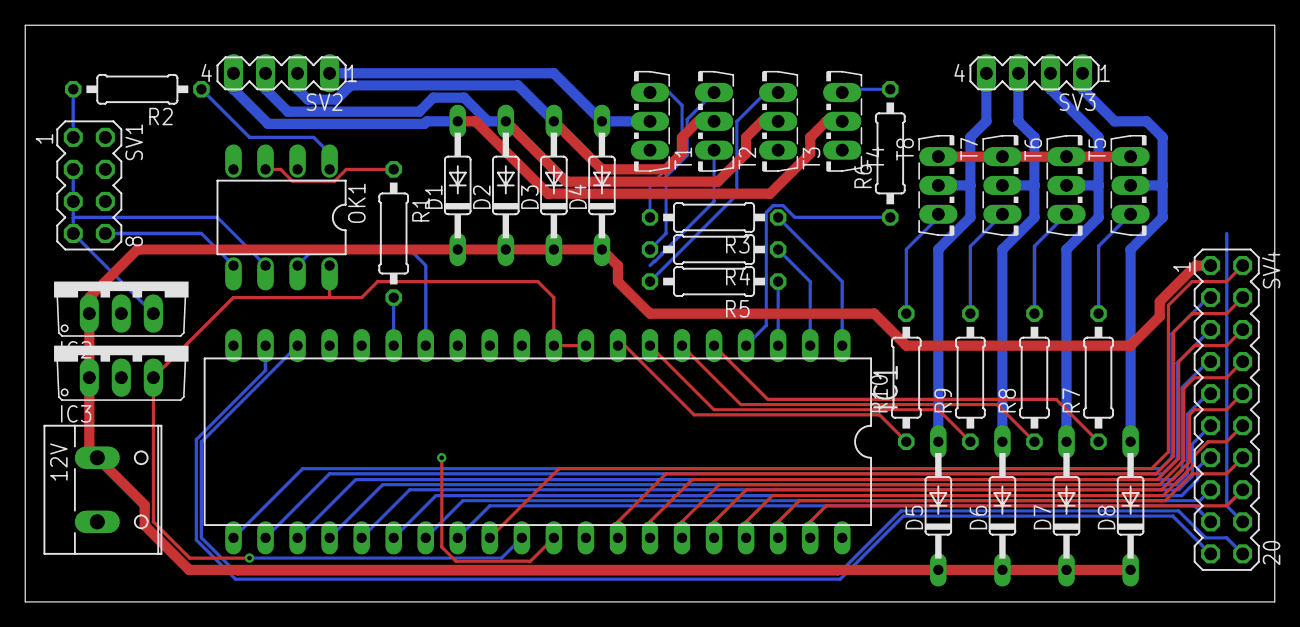
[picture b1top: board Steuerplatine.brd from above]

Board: 2 copper layers, 99.1 x 45.7 mm, 35 parts (0 on the bottom side), 52 nets.

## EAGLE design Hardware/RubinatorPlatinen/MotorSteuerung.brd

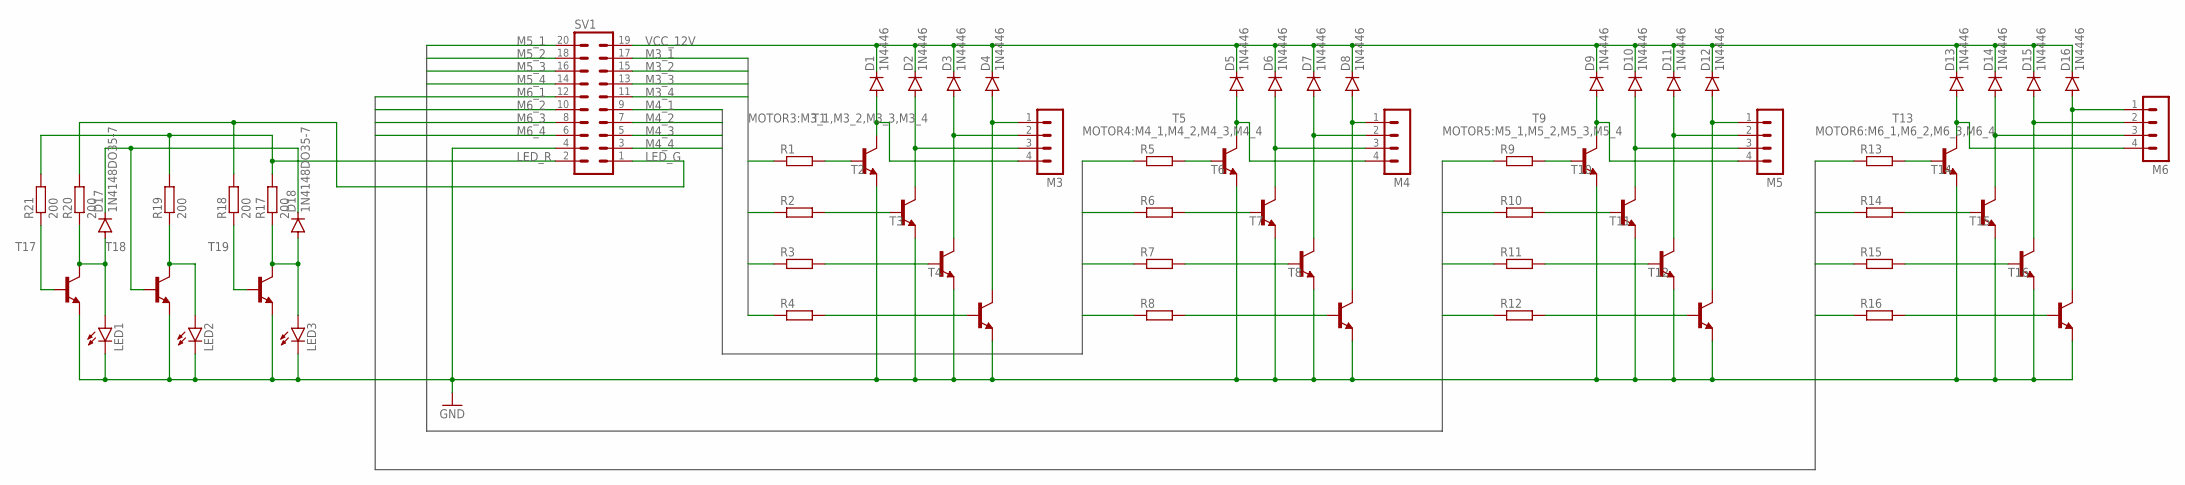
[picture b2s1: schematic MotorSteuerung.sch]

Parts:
D1, D2, D3, D4, D5, D6, D7, D8, D9, D10, D11, D12, D13, D14, D15, D16: 1N4446; DO35-10
D17, D18: 1N4148DO35-7; DO35-7
LED1, LED2, LED3: LED3MM
M3, M4, M5, M6: MA04-1
R1, R2, R3, R4, R5, R6, R7, R8, R9, R10, R11, R12, R13, R14, R15, R16: R-EU_0207/10; 0207/10
R17, R18, R19, R20, R21: 200; 0207/10
SV1: MA10-2
T1, T2, T3, T4, T5, T6, T7, T8, T9, T10, T11, T12, T13, T14, T15, T16: -NPN-TO126V; TO126V
T17, T18, T19: -NPN-TO92; TO92

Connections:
GND: LED1.K (C), LED2.K (C), LED3.K (C), SV1.4, T1.1 (E), T2.1 (E), T3.1 (E), T4.1 (E), T5.1 (E), T6.1 (E), T7.1 (E), T8.1 (E), T9.1 (E), T10.1 (E), T11.1 (E), T12.1 (E), T13.1 (E), T14.1 (E), T15.1 (E), T16.1 (E), T17.1 (E), T18.1 (E), T19.1 (E)
LED_G: R18.2, R20.2, SV1.1
LED_R: R17.2, R19.2, R21.2, SV1.2
M3_1: R1.1, SV1.17
M3_2: R2.1, SV1.15
M3_3: R3.1, SV1.13
M3_4: R4.1, SV1.11
M4_1: R5.1, SV1.9
M4_2: R6.1, SV1.7
M4_3: R7.1, SV1.5
M4_4: R8.1, SV1.3
M5_1: R9.1, SV1.20
M5_2: R10.1, SV1.18
M5_3: R11.1, SV1.16
M5_4: R12.1, SV1.14
M6_1: R13.1, SV1.12
M6_2: R14.1, SV1.10
M6_3: R15.1, SV1.8
M6_4: R16.1, SV1.6
unnamed: D1.A, M3.4, T1.2 (C)
unnamed: D2.A, M3.3, T2.2 (C)
unnamed: D3.A, M3.2, T3.2 (C)
unnamed: D4.A, M3.1, T4.2 (C)
unnamed: R1.2, T1.3 (B)
unnamed: R2.2, T2.3 (B)
unnamed: R3.2, T3.3 (B)
unnamed: R4.2, T4.3 (B)
unnamed: D5.A, M4.4, T5.2 (C)
unnamed: D6.A, M4.3, T6.2 (C)
unnamed: D7.A, M4.2, T7.2 (C)
unnamed: D8.A, M4.1, T8.2 (C)
unnamed: R5.2, T5.3 (B)
unnamed: R6.2, T6.3 (B)
unnamed: R7.2, T7.3 (B)
unnamed: R8.2, T8.3 (B)
unnamed: D9.A, M5.4, T9.2 (C)
unnamed: D10.A, M5.3, T10.2 (C)
unnamed: D11.A, M5.2, T11.2 (C)
unnamed: D12.A, M5.1, T12.2 (C)
unnamed: R9.2, T9.3 (B)
unnamed: R10.2, T10.3 (B)
unnamed: R11.2, T11.3 (B)
unnamed: R12.2, T12.3 (B)
unnamed: D13.A, M6.4, T13.2 (C)
unnamed: D14.A, M6.3, T14.2 (C)
unnamed: D15.A, M6.2, T15.2 (C)
unnamed: D16.A, M6.1, T16.2 (C)
unnamed: R13.2, T13.3 (B)
unnamed: R14.2, T14.3 (B)
unnamed: R15.2, T15.3 (B)
unnamed: R16.2, T16.3 (B)
unnamed: D18.A, LED3.A, R17.1, T19.3 (C)
unnamed: LED2.A, R19.1, T18.3 (C)
unnamed: D17.A, LED1.A, R20.1, T17.3 (C)
unnamed: D17.C, D18.C, T18.2 (B)
unnamed: R21.1, T17.2 (B)
unnamed: R18.1, T19.2 (B)
VCC_12V: D1.C, D2.C, D3.C, D4.C, D5.C, D6.C, D7.C, D8.C, D9.C, D10.C, D11.C, D12.C, D13.C, D14.C, D15.C, D16.C, SV1.19

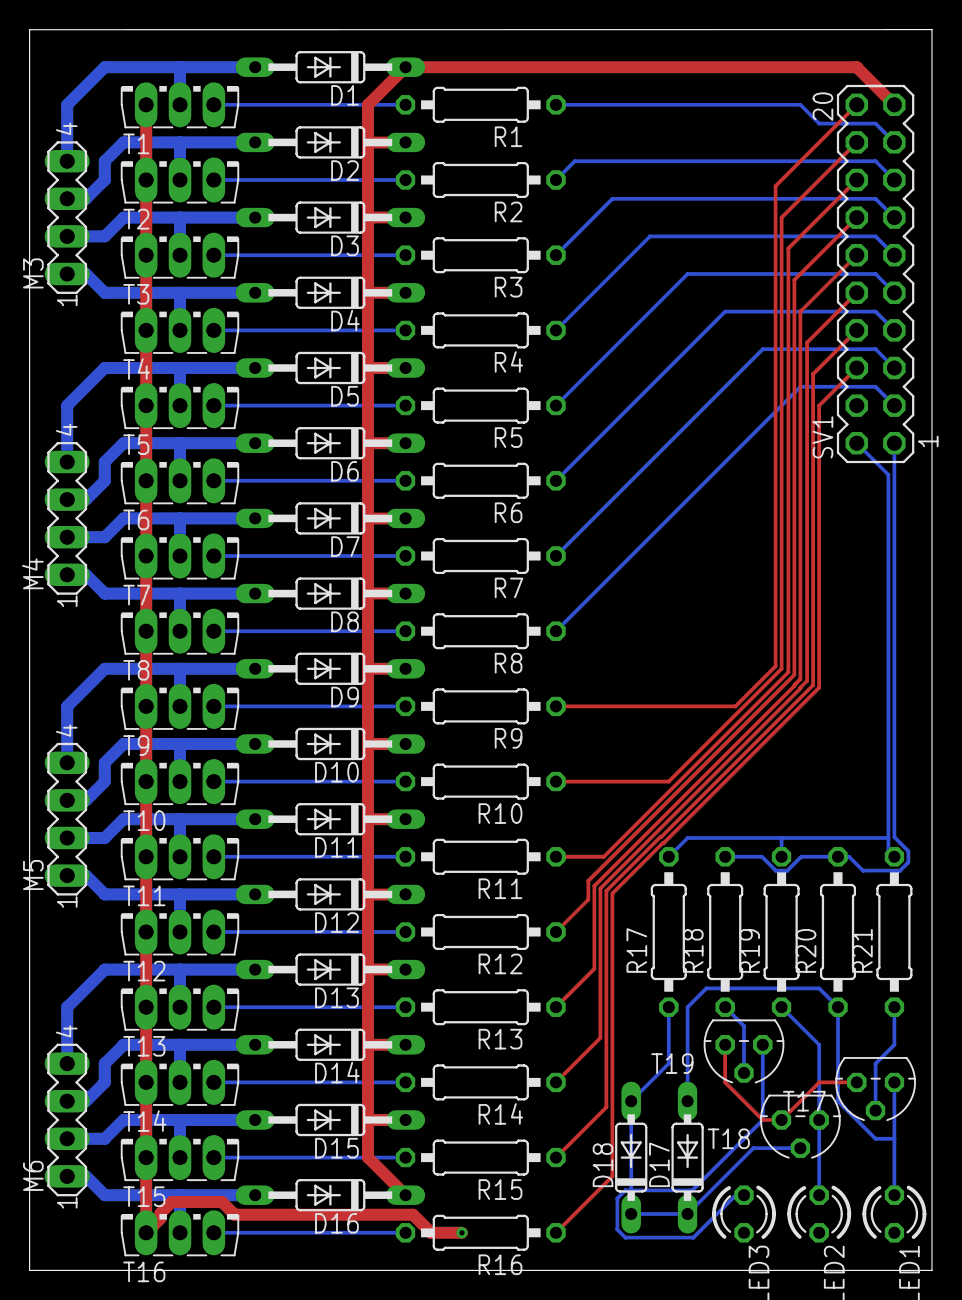
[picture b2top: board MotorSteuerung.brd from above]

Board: 2 copper layers, 61.0 x 83.8 mm, 66 parts (0 on the bottom side), 58 nets.

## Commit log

2019-08-21 GITIGNORE und GITATTRIBUTES hinzufügen.
2019-08-21 Projektdateien hinzufügen.
2019-08-22 Add Files From Rubinator Project
2019-08-22 Prepare Main Window for OpenGL
2019-08-23 Add lost Files
2019-08-23 Proting to .Net Framework
2019-08-23 Porting to .Net Framework 4.7.2
2019-08-24 Fix .csproj
2019-08-24 Graphics and events ported to GLControl
2019-08-24 Fix Merge
2019-08-24 Finished 2D system, models still todo Cleaned up some transformations and naming Created flat shaders
2019-08-24 2D view and view selection finished
2019-08-25 Fix Close Bug
2019-08-25 Implement Log on MainWindow
2019-08-25 Fix Log Bug
2019-08-26 Added log stuff, fixed lighting and mainwindow=null bug on log call
2019-08-28 Work on Menu
2019-08-28 Fix shuffle rendering in animation thread
2019-08-28 Work on Undo and Redo
2019-08-28 Finished 2d window invalidating on shuffle
2019-08-28 understanding session
2019-08-30 Overwork move implementation
2019-08-30 Implement EdgeStone
2019-08-30 Start with white cross
2019-09-09 Fix some bugs
2019-09-20 Remove unnecessary code and GUI functions
2019-09-21 Removed setState
2019-09-21 Add Arduino communication
2019-09-21 Add compiling references
2019-09-24 Cube constructor
2019-09-24 Start working on white cross
2019-09-24 Start CubeScan implementation
2019-09-25 MainWindow rework
2019-09-25 nextFix
2019-09-25 camera exception handling
2019-09-25 Working on white cross
2019-09-26 color recognition
2019-09-27 more efficent camera stream
2019-09-27 bitmap processing fixes, reduces ram usage
2019-09-28 Finish white cross
2019-09-29 Fix MoveCollection
2019-09-29 finisished color identification
2019-09-29 Added more LogStuff
2019-09-29 Add animationTime setting
2019-09-30 Prepare cross solver debug
2019-09-30 Gui-Rework
2019-09-30 Readding menu
2019-09-30 Manual Position Adding
2019-09-30 Color Identification Fixes
2019-09-30 Color Identifaction Fixes 2
2019-10-02 making the color identifaction work
2019-10-05 Simplified drawing
2019-10-05 Make window context current
2019-10-05 color ident. code cleanup
2019-10-07 Tolles Zeug
2019-10-07 Fixed decimal point parsing
2019-10-07 Fix ReadPositions
2019-10-07 Fix Scroll Delta
2019-10-07 Fixed orange color loss on vec4 cast
2019-10-07 Fix MainWindow Style
2019-10-07 Remove bin and obj
2019-10-07 Start work on LastLayer Solving
2019-10-07 Performance increase on animation thread (made into a task)
2019-10-08 Add MoveCollection Parsing
2019-10-08 Work on Last Layer Solving
2019-10-08 Implement Last Layer Solving
2019-10-09 Replaced Console with Log
2019-10-10 Work on white cross
2019-10-11 Fix moves and add move shortcuts
2019-10-11 Implement white cross
2019-10-11 fix .gitignore
2019-10-11 Fix move drawing
2019-10-11 Optimize MoveCollection
2019-10-11 Fix opimized MoveCollection
2019-10-12 Fix white cross
2019-10-12 Fix menu style
2019-10-12 implement CornerStones
2019-10-13 start with FTL
2019-10-14 Start to implement FTLSlot
2019-10-14 Work on FTL
2019-10-14 start implementation of FTL cases
2019-10-22 Add some unnecessary stuff
2019-10-27 Add 3D Model
2019-10-27 Add actual 3D files
2019-10-29 Work on 3D Model
2019-11-05 Implement 'Eagle' Case
2019-11-05 Add components list
2019-11-06 update partslist
2019-11-14 Work on F2L
2019-11-15 F2L Corner White down
2019-11-15 Implement F2L cases Corner false in slot
2019-11-16 implement corner white facing up
2019-11-17 Add E-Box and Drawings
2019-11-18 Debug WebCams
2019-11-18 Add Motorhalterungen
2019-11-18 Add WiFi program
2019-11-19 Add new MotorHalterungen
2019-11-19 Implement F2L
2019-11-26 compile arduino program
2019-11-26 debug F2L cases
2019-11-27 Finish F2L
2019-11-27 fix pll solving
2019-11-28 Make Solving async and work on last layer solving
2019-11-29 Update Oll Patterns
2019-11-29 Fix Cube Solving
2019-11-29 Make solving ssync and add move history
2019-11-30 Split project
2019-11-30 optimize solving
2019-12-02 Add log Thread
2019-12-02 Work on microcontroller communication
2019-12-04 Add communication protocol
2019-12-09 Add IO support on ATMEGA16
2019-12-09 implement Serial
2019-12-13 Add IO and Serial communication
2019-12-13 Finish microcontroller programming
2019-12-14 BehebmalBasti
2019-12-15 Refaftoring and Commenting of CubeScan
2019-12-15 CAD Stuff
2019-12-15 Add Software Folder
2019-12-16 Implement Arduino Mega for 'MINT-Messe'
2019-12-16 Temporary fix for weird isPrime system
2019-12-16 Remove ESP8266 code
2019-12-18 Fix Problems for 'MINT-Messe'
2019-12-18 Started refactoring
2019-12-19 Removed isPrime
2019-12-20 Added MoveSynchronization and wrapped arduino
2019-12-21 fix move parsing
2019-12-21 Finished graphics error and logThread joining, introduced timeout on arduino
2019-12-27 Overwork cube rotations
2019-12-27 Add Move logging
2019-12-27 Fix cube solving algorithm
2020-01-04 Fix .csproj and optimize face rotation
2020-01-04 Remove unused OLL pattern
2020-01-08 DrawCube MultiTurn
2020-01-08 Added Pie charts
2020-01-08 Add MultiTurn setting
2020-01-08 define Camera
2020-01-08 Add arduino multi turns
2020-01-08 Camera and PieChart fixes
2020-01-09 Implement multi turn move synchronisation
2020-01-10 Fix Arduinoprogram
2020-01-10 Add changes, todo: fix draw moves
2020-01-10 Fix multiturn steppers
2020-01-10 Fix draw moves
2020-01-10 F2L Debug
2020-01-13 Remove unused Mikrocontroller program
2020-01-14 Manual Cube Generation From Camera-Streams and GUI-Name-Refactoring
2020-01-14 Fix debug menu
2020-01-14 Overwork Log system
2020-01-14 Fix release mode
2020-01-14 fix logging
2020-01-14 Added RefColors
2020-01-14 Remove debug code
2020-01-24 ReadPosition dynamic
2020-01-24 Create app project
2020-01-24 Extract RubinatorCore Library
2020-01-24 Android add CubeDrawing
2020-01-26 Work on CubeDrawing
2020-01-26 Remove Errors
2020-01-26 New Project
2020-01-26 Work on CubeView
2020-01-26 Adding Camera - not working yet
2020-01-27 Work on 3D View
2020-01-27 Implement CubeView
2020-01-27 Work on Texture loading
2020-01-27 Fix fragment Shader
2020-01-27 CameraPreview Stuff
2020-01-28 Fix Builderrors
2020-01-28 Add controls page
2020-01-28 Fix packages
2020-01-28 GUI-Framework
2020-01-29 Add cube rotation
2020-01-29 Add bluetooth device selection
2020-01-30 Use VertexArrayObjects
2020-01-30 Add bluetooth server and connect button
2020-01-31 Fix OpenGL ES Errors
2020-02-01 Finished bluetooth communication
2020-02-01 Fix rotations
2020-02-01 Fix Touch Rotations
2020-02-02 Fix CubeView Inputs
2020-02-02 Wire up bluetooth control backend
2020-02-03 Simplified graphics
2020-02-07 Finished downsync
2020-02-07 Comment and Refactor
2020-02-08 Optimize CubeSolving
2020-02-08 Comment and refactor F2L
2020-02-09 Some work
2020-02-10 Finished two way cube syncing
2020-02-10 MultiTurn bug remaining
2020-02-10 Reworked GUI and added server-client debug log
2020-02-10 Fix MultiTurn byte conversion
2020-02-11 Rename F2L
2020-02-11 Add Move Delay
2020-02-12 Arduino responses and color values
2020-02-12 GUI and LEDs
2020-02-14 Fix Arduino and other stuff
2020-02-14 Fix last problems
2020-02-16 JuFo
2020-02-17 Start work on bluetooth packet system
2020-02-17 Add Save Images
2020-02-21 Reduce arduino step delay
2020-02-21 Reduce Move Delay
2020-02-22 First Steps New Color ID
2020-02-23 Implemented new color identifaction - no fixes yet
2020-02-23 Implementation of new camera-streams and namespace-refactoring in whole project
2020-02-23 Added " Switch CameraPreviews per Drag and Drop"
2020-02-23 Implemented ReadPositionAdding and many, many fixes
2020-02-23 mini-commit - xml-start
2020-02-24 Finished bluetooth framework
2020-02-24 Update move protocol
2020-02-25 Refactor Arduino stuff
2020-02-27 many fixes and swap per drag and drop implemented
2020-02-28 Arduino packet communication
2020-02-29 Adding whats missing
2020-02-29 Add new Arduino program
2020-02-29 Fix arduino
2020-03-08 Work on arduino program
2020-03-08 Add LCD Display
2020-07-11 Add Jugend_Forscht_Arbeit.pdf
2020-11-17 Fix Readme
2020-11-24 Create LICENSE
2021-11-04 fix typo
2022-01-21 Fix broken link and readme formatting
